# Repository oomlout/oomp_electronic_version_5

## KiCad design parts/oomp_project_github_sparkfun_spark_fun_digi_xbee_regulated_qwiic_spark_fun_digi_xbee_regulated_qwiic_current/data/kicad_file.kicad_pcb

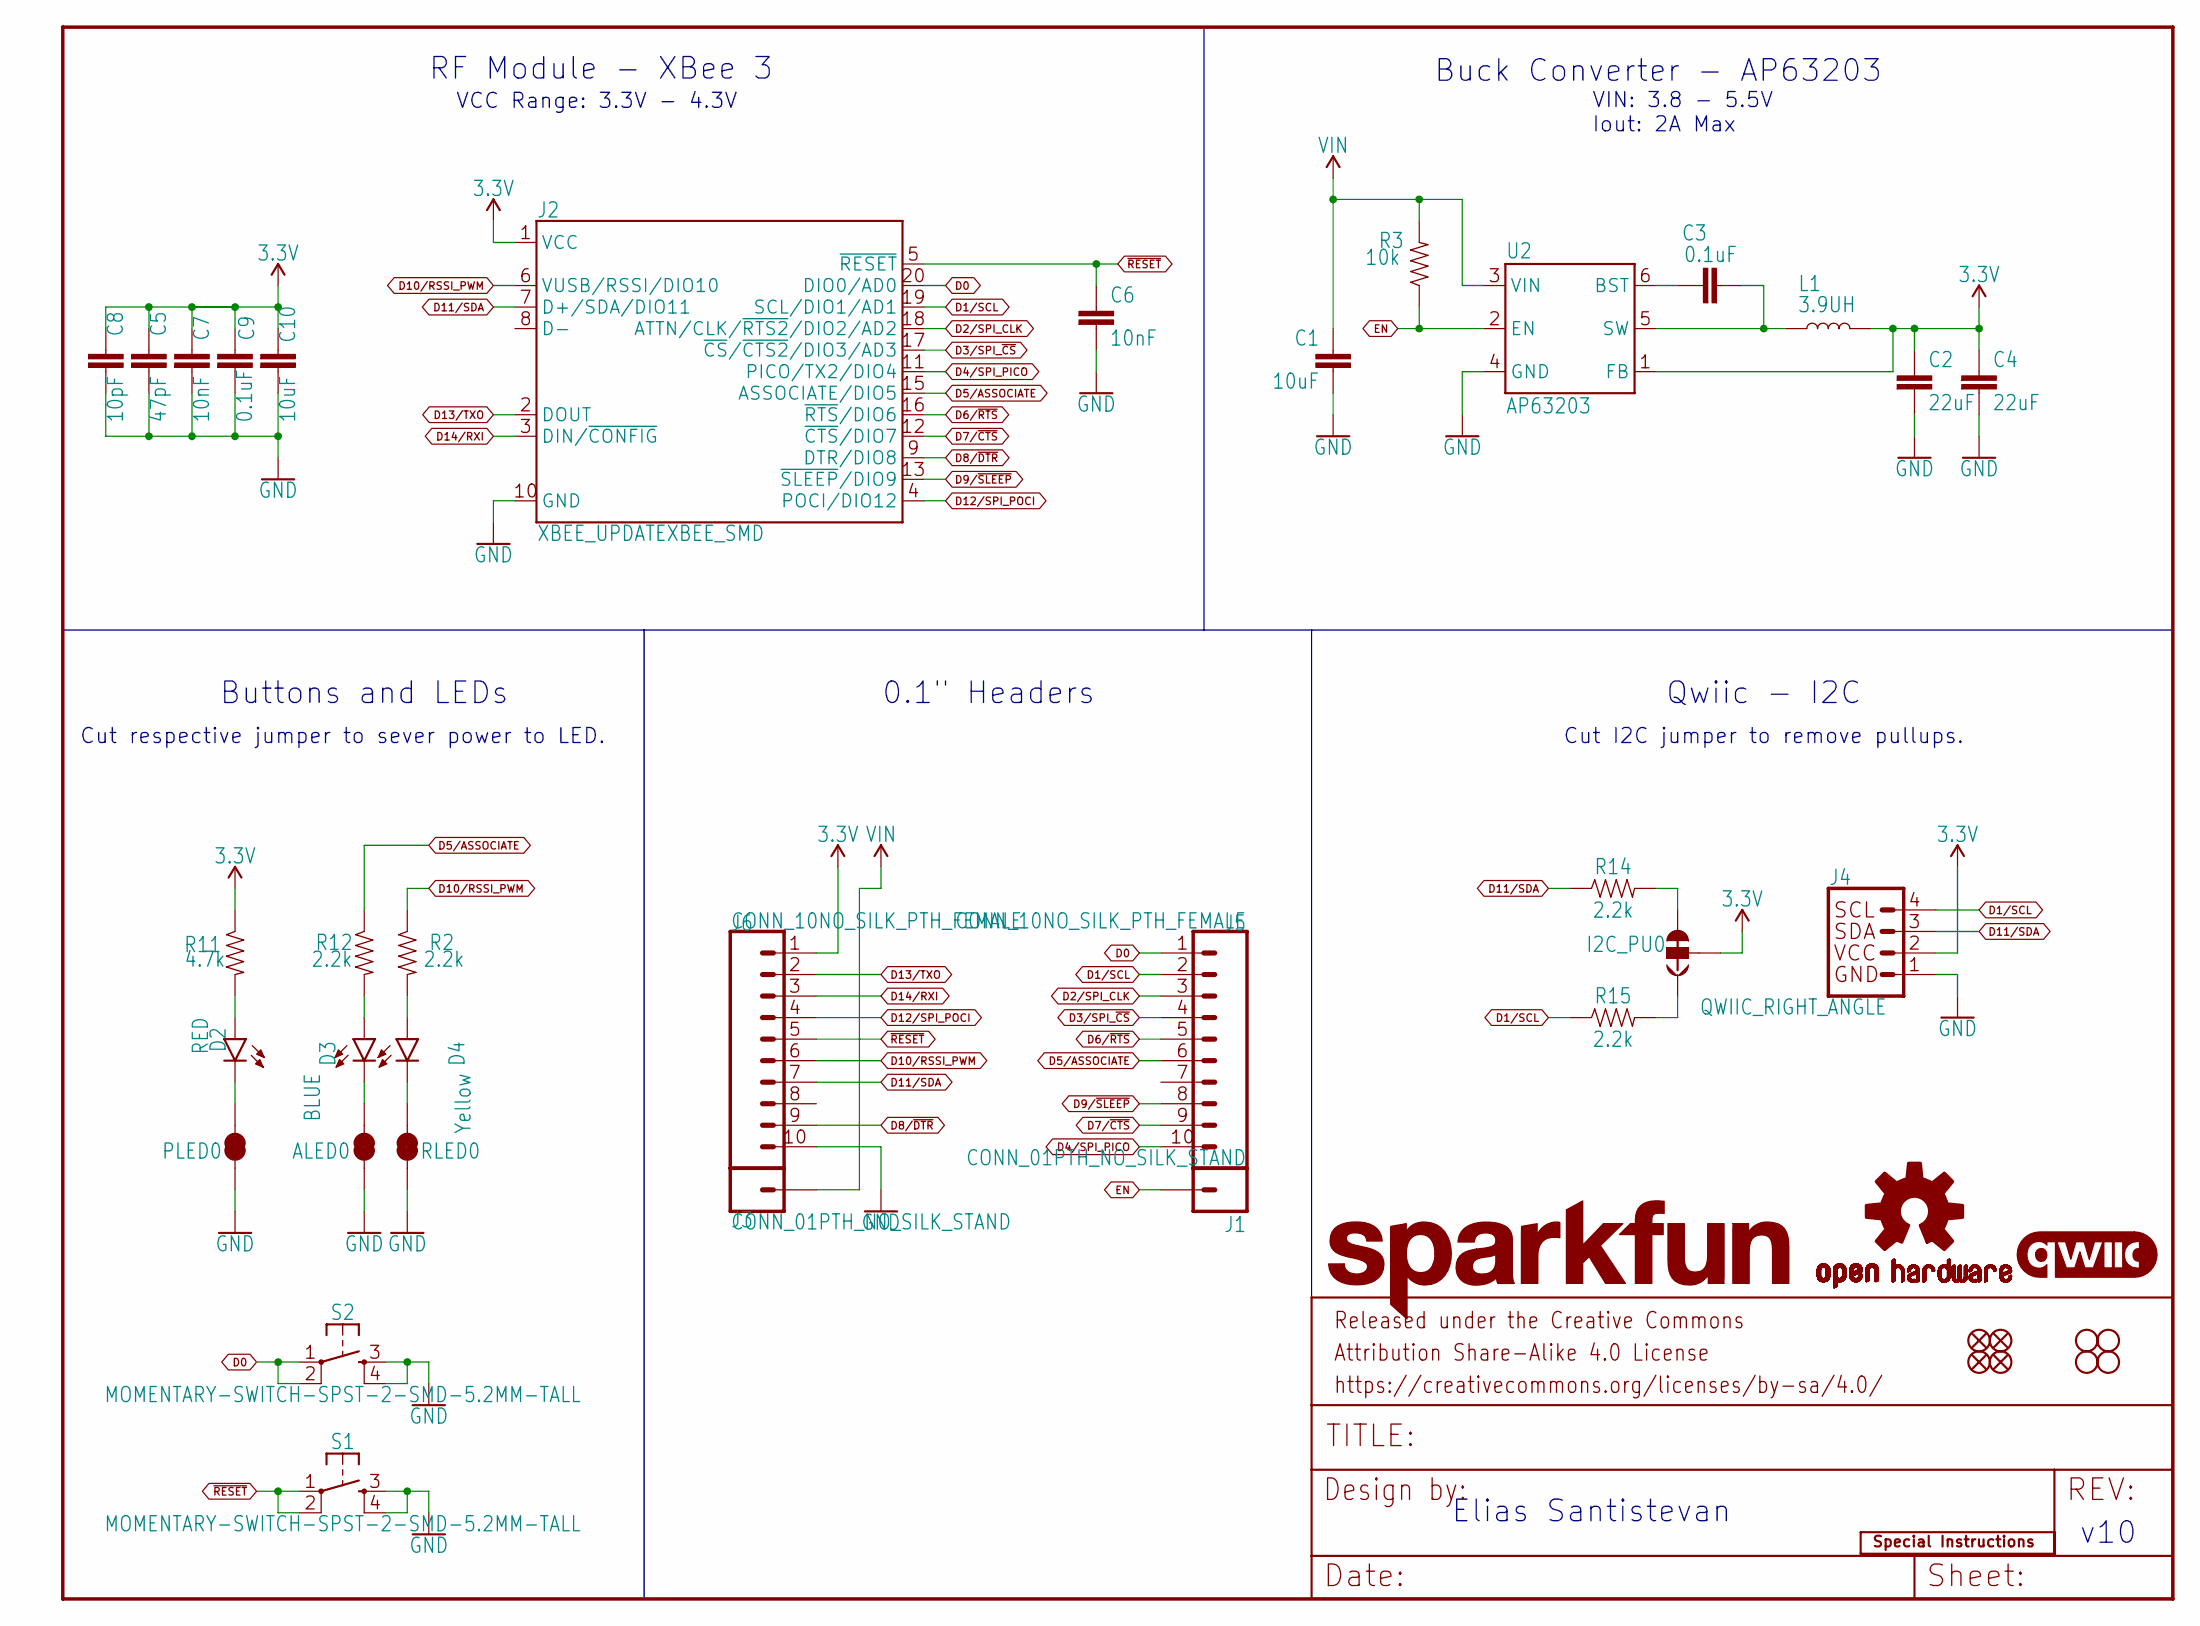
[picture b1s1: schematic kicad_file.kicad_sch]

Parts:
ALED0: JUMPER-SMT_2_NC_TRACE_SILK; SMT-JUMPER_2_NC_TRACE_SILK
C1: 10uF; 1210
C2, C4: 22uF; 0603
C3, C9: 0.1uF; 0603
C5: 47pF; 0603
C6, C7: 10nF; 0603
C8: 10pF; 0603
C10: 10uF; 0603
D2: RED; LED-0603
D3: BLUE; LED-0603
D4: Yellow; LED-0603
FD1, FD2, FD3, FD4: FIDUCIAL1X2; FIDUCIAL-1X2
FRAME2: FRAME-LETTER; CREATIVE_COMMONS
H1, H2, H3, H4: STAND-OFFTIGHT; STAND-OFF-TIGHT
I2C_PU0: JUMPER-SMT_3_2-NC_TRACE_SILK; SMT-JUMPER_3_2-NC_TRACE_SILK
J1, J3: CONN_01PTH_NO_SILK_STAND; 1X01_NO_SILK_STAND
J2: XBEE_UPDATEXBEE_SMD; XBEE3-SMD
J4: QWIIC_RIGHT_ANGLE; JST04_1MM_RA
J5, J6: CONN_10NO_SILK_PTH_FEMALE; 1X10_NO_SILK
L1: 3.9UH; INDUCTOR_3.9UH
LOGO1: SPECIAL_INSTRUCTIONS-ORDERING; ORDERING_INSTRUCTIONS
LOGO2: OSHW-LOGOS; OSHW-LOGO-S
LOGO3: QWIIC_LOGO_4MM; QWIIC_4MM
LOGO4: SFE_LOGO_NAMEBLANK; BLANK
PLED0: JUMPER-SMT_2_NC_TRACE_SILK; SMT-JUMPER_2_NC_TRACE_SILK
R2, R12, R14, R15: 2.2k; 0603
R3: 10k; 0603
R11: 4.7k; 0603
RLED0: JUMPER-SMT_2_NC_TRACE_SILK; SMT-JUMPER_2_NC_TRACE_SILK
S1, S2: MOMENTARY-SWITCH-SPST-2-SMD-5.2MM-TALL; TACTILE_SWITCH_SMD_5.2MM
U2: AP63203; SOT23-6

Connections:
3.3V: C2.1, C4.1, C5.1, C7.1, C8.1, C9.1, C10.1, I2C_PU0.2, J2.1 (VCC), J4.2, J6.1, L1.P$2 (2), R11.1, U2.1 (FB)
D0: J2.20 (DIO0/AD0), J5.1, S2.1, S2.2
D1/SCL: J2.19 (SCL/DIO1/AD1), J4.4, J5.2, R15.1
D2/SPI_CLK: J2.18 (ATTN/CLK/~RTS2/DIO2/AD2), J5.3
D3/SPI_~CS: J2.17 (~CS/~CTS2/DIO3/AD3), J5.4
D4/SPI_PICO: J2.11 (PICO/TX2/DIO4), J5.10
D5/ASSOCIATE: J2.15 (ASSOCIATE/DIO5), J5.6, R12.1
D6/~RTS: J2.16 (~RTS/DIO6), J5.5
D7/~CTS: J2.12 (~CTS/DIO7), J5.9
D8/~DTR: J2.9 (DTR/DIO8), J6.9
D9/~SLEEP: J2.13 (~SLEEP/DIO9), J5.8
D10/RSSI_PWM: J2.6 (VUSB/RSSI/DIO10), J6.6, R2.1
D11/SDA: J2.7 (D+/SDA/DIO11), J4.3, J6.7, R14.1
D12/SPI_POCI: J2.4 (POCI/DIO12), J6.4
D13/TXO: J2.2 (DOUT), J6.2
D14/RXI: J2.3 (DIN/~CONFIG), J6.3
EN: J1.1, R3.1, U2.2 (EN)
GND: ALED0.1, C1.2, C2.2, C4.2, C5.2, C6.2, C7.2, C8.2, C9.2, C10.2, J2.10 (GND), J4.1, J6.10, PLED0.1, RLED0.1, S1.3, S1.4, S2.3, S2.4, U2.4 (GND)
unnamed: C3.1, U2.6 (BST)
unnamed: D4.A, R2.2
unnamed: D4.C, RLED0.2
unnamed: D2.A, R11.2
unnamed: C3.2, L1.P$1 (1), U2.5 (SW)
unnamed: I2C_PU0.3, R14.2
unnamed: D3.A, R12.2
unnamed: I2C_PU0.1, R15.2
unnamed: ALED0.2, D3.C
unnamed: D2.C, PLED0.2
VIN: C1.1, J3.1, R3.2, U2.3 (VIN)
~RESET: C6.1, J2.5 (~RESET), J6.5, S1.1, S1.2

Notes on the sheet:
Buck Converter - AP63203
VCC Range: 3.3V - 4.3V
Elias Santistevan
0.1" Headers
RF Module - XBee 3
VIN: 3.8 - 5.5V Iout: 2A Max
Buttons and LEDs
v10
Qwiic - I2C
Cut I2C jumper to remove pullups.
Cut respective jumper to sever power to LED.

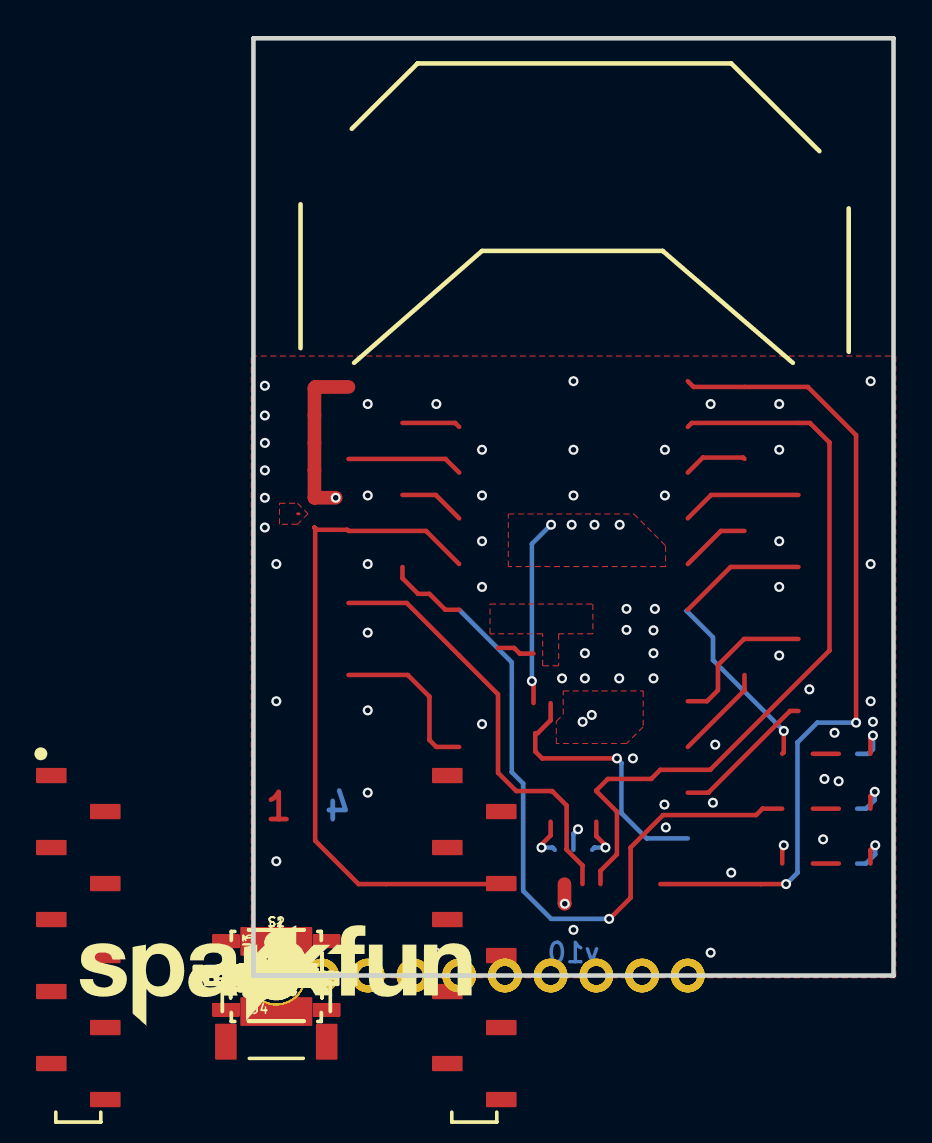
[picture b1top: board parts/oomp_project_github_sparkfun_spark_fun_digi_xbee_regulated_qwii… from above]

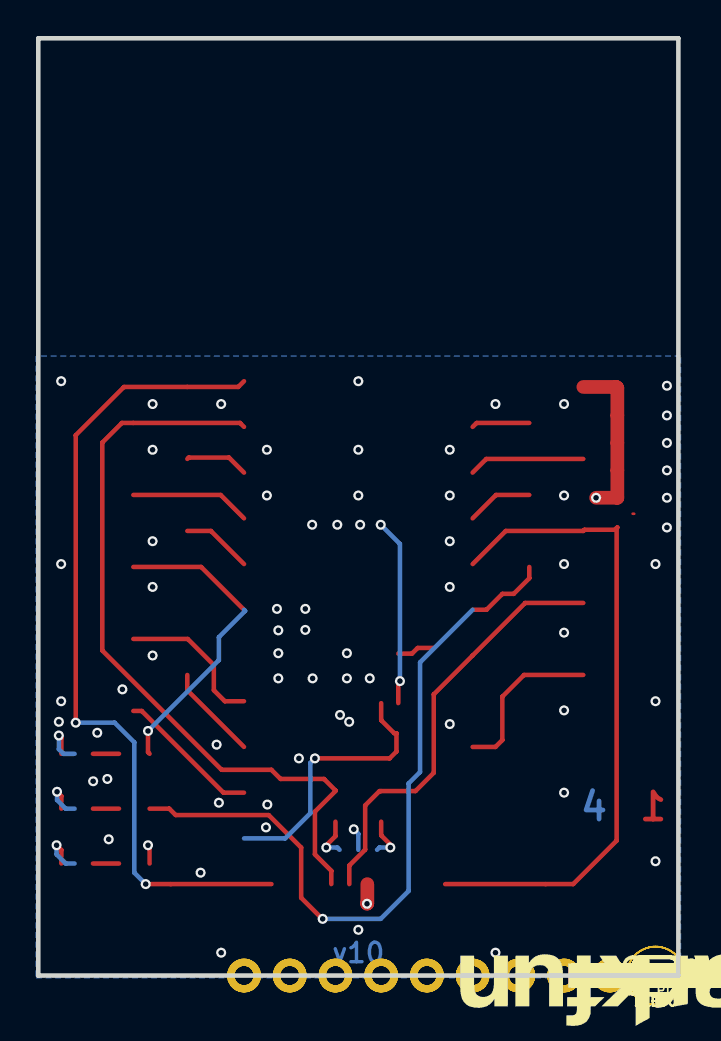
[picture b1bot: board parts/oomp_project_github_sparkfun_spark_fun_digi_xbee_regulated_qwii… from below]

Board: 4 copper layers, 35.6 x 52.1 mm, 98 parts (36 on the bottom side), 30 nets.

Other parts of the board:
U$1, U$12: #GND#0
U$2, U$63: SFE_LOGO_NAME_.2
U$3, U$6: #EN#17
U$4: #NC#1
U$5: #NC#3
U$7: #D7##CTS##26
U$8: #D0#AD0#18
U$9, U$44: #3V3#1
U$10: #D4#PICO#25
U$11: #RLED#22
U$13: #D8##DTR##27
U$14: #RSSI#D10#17
U$15: #SDA#D11#9
U$16: ##RST##15
U$17: #POCI#D12#24
U$18: #RXI#D14#15
U$19: #D2#AD2#19
U$20: #D6##RTS##25
U$21: #TXO#8
U$22: #TXO#D13#13
U$23, U$33: EXPLORER1344
U$24, U$29: REGULATED1343
U$25, U$28: XBEE340
U$26: #I2C#33
U$27: #RXI#7
U$30: #RST#30
U$31, U$65: #D0#3
U$32: #D1#AD1#SCL#8
U$34: #D3#AD3##CS##23
U$35: #D5#ASSOC#25
U$36: #D9##SLP##28
U$40: D03
U$42: PWR26
U$43: ASSOC27
U$45: #POCI#32
U$46, U$66: #VIN#4
U$49: #ALED#21
U$52: #PLED#20
U$59: ##CS##26
U$60: #SCLK#33
U$61: SFE_LOGO_FLAME_.2
U$62: RSSI31
U$64: #SCL#9

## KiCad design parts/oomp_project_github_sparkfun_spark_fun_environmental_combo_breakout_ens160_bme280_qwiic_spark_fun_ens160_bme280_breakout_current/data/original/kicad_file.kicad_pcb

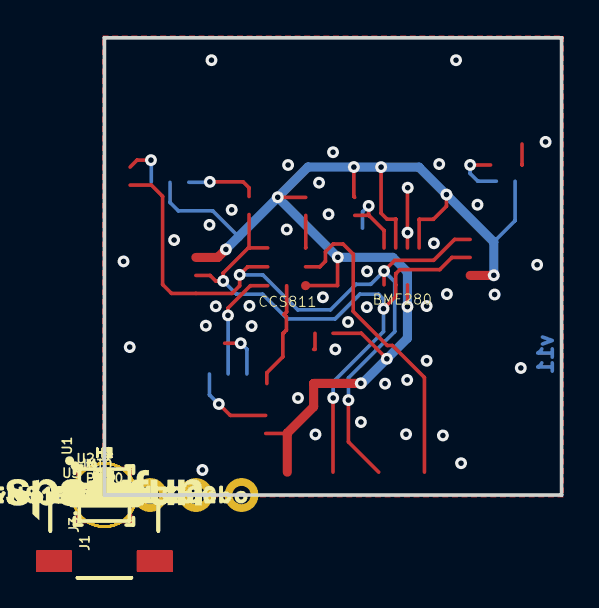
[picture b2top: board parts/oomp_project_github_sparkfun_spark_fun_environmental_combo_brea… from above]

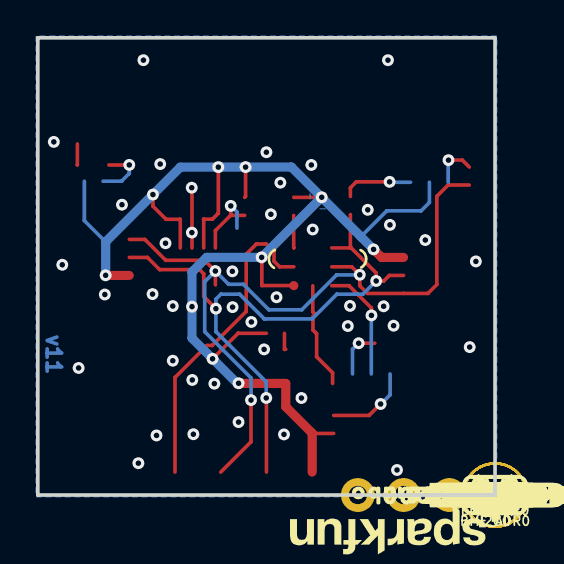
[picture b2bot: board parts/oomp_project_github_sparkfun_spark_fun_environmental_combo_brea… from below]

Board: 2 copper layers, 25.4 x 25.4 mm, 67 parts (25 on the bottom side), 16 nets.

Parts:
BME_ADR0: SMT-JUMPER_2_NO_SILK
C1, C3, C6: 0.1uF; 0402-TIGHT
C2, C5: 1.0uF; 0402-TIGHT
C4: 10uF; 0402-TIGHT
ENS_ADR0: JUMPER-SMT_3_1-NC_TRACE_SILK; SMT-JUMPER_3_1-NC_TRACE_SILK
FD1, FD2, FD3, FD4: FIDUCIAL1X2; FIDUCIAL-1X2
FRAME1: FRAME-LETTER; CREATIVE_COMMONS
H1, H2, H3, H4: STAND-OFF
I2C0: SMT-JUMPER_3_2-NC_TRACE_SILK
INT0: 1X01_NO_SILK_STAND
J1, J3: Qwiic Right Angle; JST04_1MM_RA
J4: PTH; 1X04_NO_SILK
LED0: SMT-JUMPER_2_NC_TRACE_SILK
LOGO1: SFE_LOGO_NAME.1_INCH; SFE_LOGO_NAME_.1
LOGO2: REVISION
LOGO3: SFE_LOGO_NAME.1_INCH; SFE_LOGO_NAME_.1@1
LOGO4: OSHW-LOGOS; OSHW-LOGO-S
PWR0: RED; LED-0603
R1, R6, R7, R8: 10k; 0402-TIGHT
R2: 4.7k; 0402-TIGHT
R3: 100k; 0402-TIGHT
R13, R14: 2.2k; 0402-TIGHT
U1: AP2127K-1.8V; SOT23-5
U2: ENS160; LGA-9
U3: BME280; LGA-8-2.5X2.5
U$1: #BME_ADR#0
U$2: #0X53#0
U$3: #0X52#0
U$4: ##INT##6
U$5: #ENS_ADR#0
U$6: #I2C#0
U$7, U$11: ENVIRONMENTAL_COMBO0
U$8: #SCL#4
U$9: #GND#2
U$10, U$12: ENS160_#_BME2800
U$13, U$61: DEFAULT0
U$14: #SDA#3
U$15: #PWR#0
U$16: OPEN#0X770
U$17: CLOSED#0X760
U$18: #LED#0
U$20, U$21: QWIIC_4MM
U$27, U$46: #3V3#874
U$45: #GND#864
U$47: #SDA#874
U$48: #SCL#875
U$51: ##INT##877
U$59: ORDERING_INSTRUCTIONS

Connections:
1.8V: C4.1, C5.1, U1.5, U2.P4
3.3V: C1.1, C2.1, C3.1, C6.1, I2C0.2, J1.2, J3.2, J4.2, LED0.1, R1.2, R3.2, R6.2, R8.2, U1.1, U2.P5, U3.2, U3.6, U3.8
ADDR: ENS_ADR0.2, U2.P3
GND: BME_ADR0.1, C1.2, C2.2, C3.2, C4.2, C5.2, C6.2, J1.1, J3.1, J4.1, R2.1, R7.1, U1.2, U2.P8, U2.P9, U3.1, U3.7
unnamed: ENS_ADR0.3, R8.1
unnamed: R1.1, U1.3
unnamed: I2C0.3, R13.2
unnamed: I2C0.1, R14.2
unnamed: PWR0.C, R2.2
unnamed: ENS_ADR0.1, R7.2
unnamed: LED0.2, PWR0.A
SCL: J1.4, J3.4, J4.4, R14.1, U2.P2, U3.4
SDA: J1.3, J3.3, J4.3, R13.1, U2.P1, U3.3
SDO/ADR: BME_ADR0.2, R3.1, U3.5
~CS: R6.1, U2.P7
~INT: INT0.1, U2.P6

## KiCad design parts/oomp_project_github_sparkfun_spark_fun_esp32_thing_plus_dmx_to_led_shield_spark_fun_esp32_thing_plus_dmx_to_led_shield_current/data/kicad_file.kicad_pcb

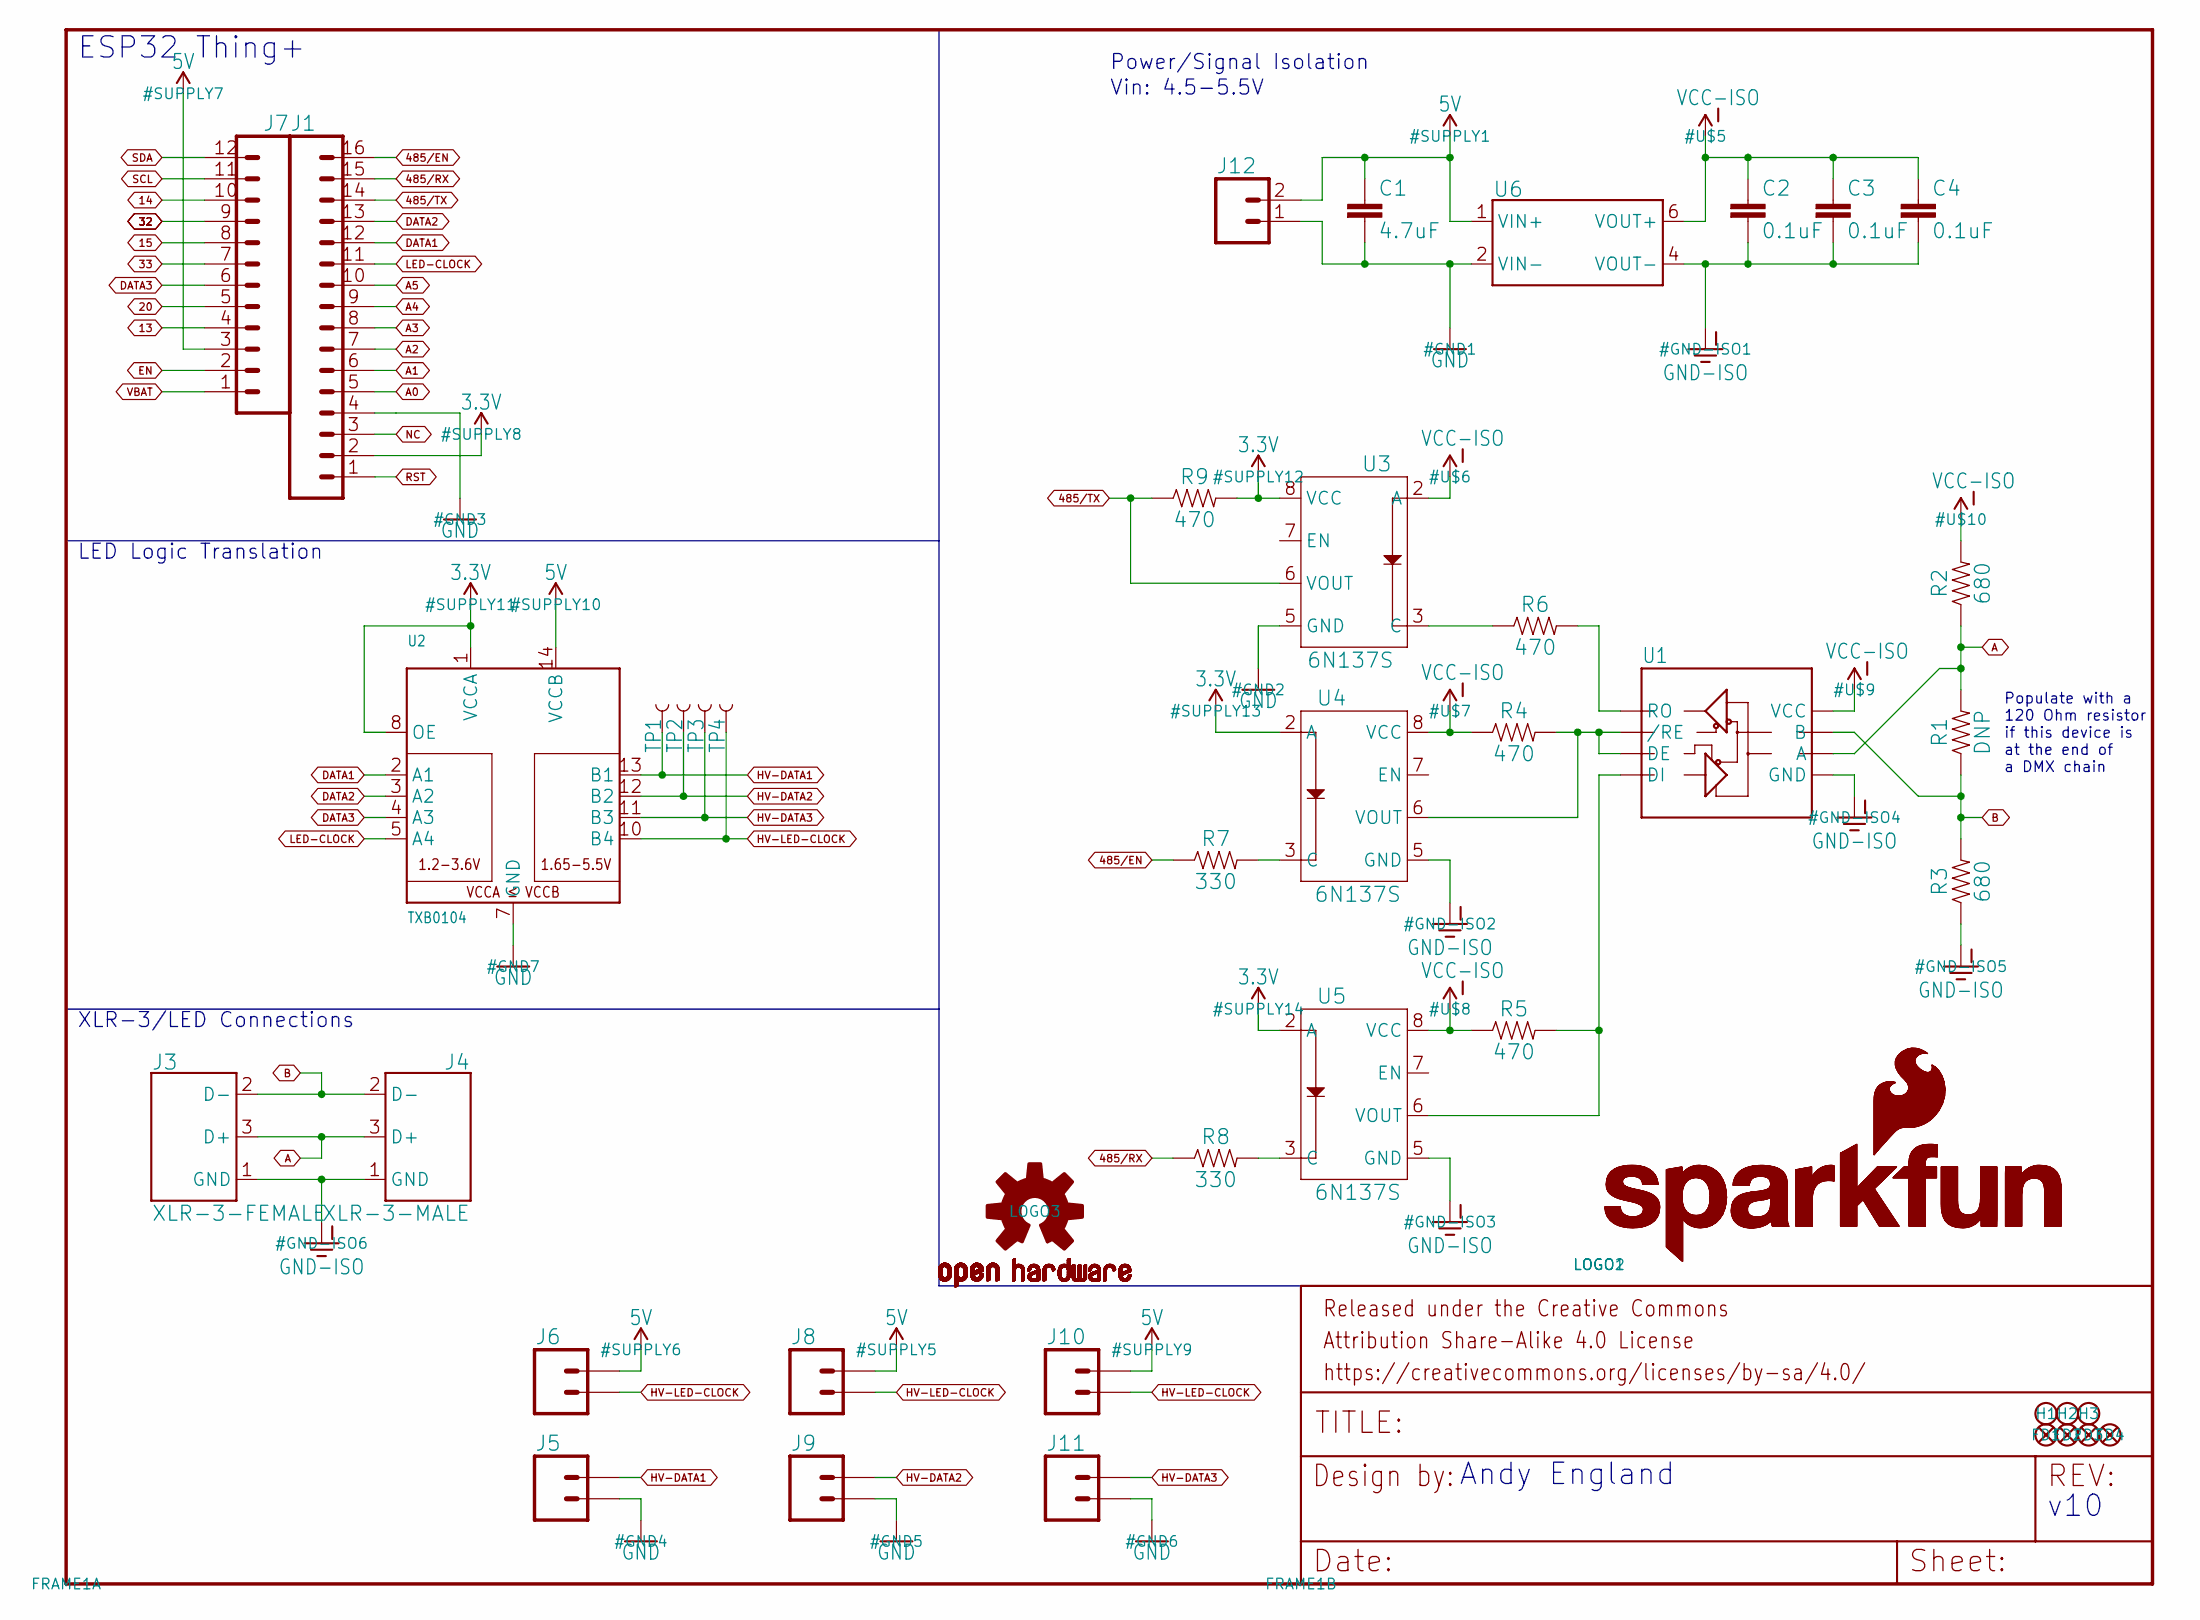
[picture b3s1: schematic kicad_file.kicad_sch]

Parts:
C1: 4.7uF; 0603
C2, C3, C4: 0.1uF; 0603
FD1, FD2, FD3, FD4: FIDUCIALUFIDUCIAL; FIDUCIAL-MICRO
FRAME1: FRAME-LETTER; CREATIVE_COMMONS
H1, H2, H3: STAND-OFFTIGHT; STAND-OFF-TIGHT
J1: CONN_16LOCK_NO_SILK; 1X16_LOCK_NO_SILK
J3: XLR-3-FEMALE; XLR-3_FEMALE
J4: XLR-3-MALE; XLR-3_MALE
J5, J6, J8, J9, J10, J11: CONN_02SMALL_POKEHOME; 1X02_POKEHOME
J7: CONN_12LOCK_NO_SILK; 1X12_LOCK_NO_SILK
J12: CONN_023.5MM; SCREWTERMINAL-3.5MM-2
LOGO1, LOGO2: SFE_LOGO_NAME_FLAME.2_INCH; SFE_LOGO_NAME_FLAME_.2
LOGO3: OSHW-LOGOS; OSHW-LOGO-S
R1: DNP; AXIAL-0.3EZ
R2, R3: 680; 0603
R4, R5, R6, R9: 470; 0603
R7, R8: 330; 0603
TP1, TP2, TP3, TP4: TEST-POINT3; PAD.03X.03
U1: MAX3485CSA; SO08
U2: TXB0104; TSSOP14
U3, U4, U5: 6N137S; 8-SMD
U6: RFB-0505S

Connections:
3.3V: J1.2, R9.2, U2.1 (VCCA), U2.8 (OE), U3.8 (VCC), U4.2 (A), U5.2 (A)
5V: C1.1, J6.P2 (2), J6.P4 (2), J7.3, J8.P2 (2), J8.P4 (2), J10.P2 (2), J10.P4 (2), J12.2, U2.14 (VCCB), U6.1 (VIN+)
13: J7.4
14: J7.10
15: J7.8
20: J7.5
32: J7.9
33: J7.7
485/EN: J1.16, R7.1
485/RX: J1.15, R8.1
485/TX: J1.14, R9.1, U3.6 (VOUT)
A: J3.3 (D+), J4.3 (D+), R1.P$2 (2), R2.1, U1.6 (A)
A0: J1.5
A1: J1.6
A2: J1.7
A3: J1.8
A4: J1.9
A5: J1.10
B: J3.2 (D-), J4.2 (D-), R1.P$1 (1), R3.2, U1.7 (B)
DATA1: J1.12, U2.2 (A1)
DATA2: J1.13, U2.3 (A2)
DATA3: J7.6, U2.4 (A3)
EN: J7.2
GND: C1.2, J1.4, J5.P1 (1), J5.P3 (1), J9.P1 (1), J9.P3 (1), J11.P1 (1), J11.P3 (1), J12.1, U2.7 (GND), U3.5 (GND), U6.2 (VIN-)
GND-ISO: C2.2, C3.2, C4.2, J3.1 (GND), J4.1 (GND), R3.1, U1.5 (GND), U4.5 (GND), U5.5 (GND), U6.4 (VOUT-)
HV-DATA1: J5.P2 (2), J5.P4 (2), TP1.P$1, U2.13 (B1)
HV-DATA2: J9.P2 (2), J9.P4 (2), TP2.P$1, U2.12 (B2)
HV-DATA3: J11.P2 (2), J11.P4 (2), TP3.P$1, U2.11 (B3)
HV-LED-CLOCK: J6.P1 (1), J6.P3 (1), J8.P1 (1), J8.P3 (1), J10.P1 (1), J10.P3 (1), TP4.P$1, U2.10 (B4)
LED-CLOCK: J1.11, U2.5 (A4)
unnamed: R8.2, U5.3 (C)
unnamed: R7.2, U4.3 (C)
unnamed: R4.2, U1.2 (/RE), U1.3 (DE), U4.6 (VOUT)
unnamed: R5.2, U1.4 (DI), U5.6 (VOUT)
unnamed: R6.1, U3.3 (C)
unnamed: R6.2, U1.1 (RO)
NC: J1.3
RST: J1.1
SCL: J7.11
SDA: J7.12
VBAT: J7.1
VCC-ISO: C2.1, C3.1, C4.1, R2.2, R4.1, R5.1, U1.8 (VCC), U3.2 (A), U4.8 (VCC), U5.8 (VCC), U6.6 (VOUT+)

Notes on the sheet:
v10
Andy England
Populate with a 120 Ohm resistor if this device is at the end of a DMX chain
Power/Signal Isolation
LED Logic Translation
ESP32 Thing+
Vin: 4.5-5.5V
XLR-3/LED Connections

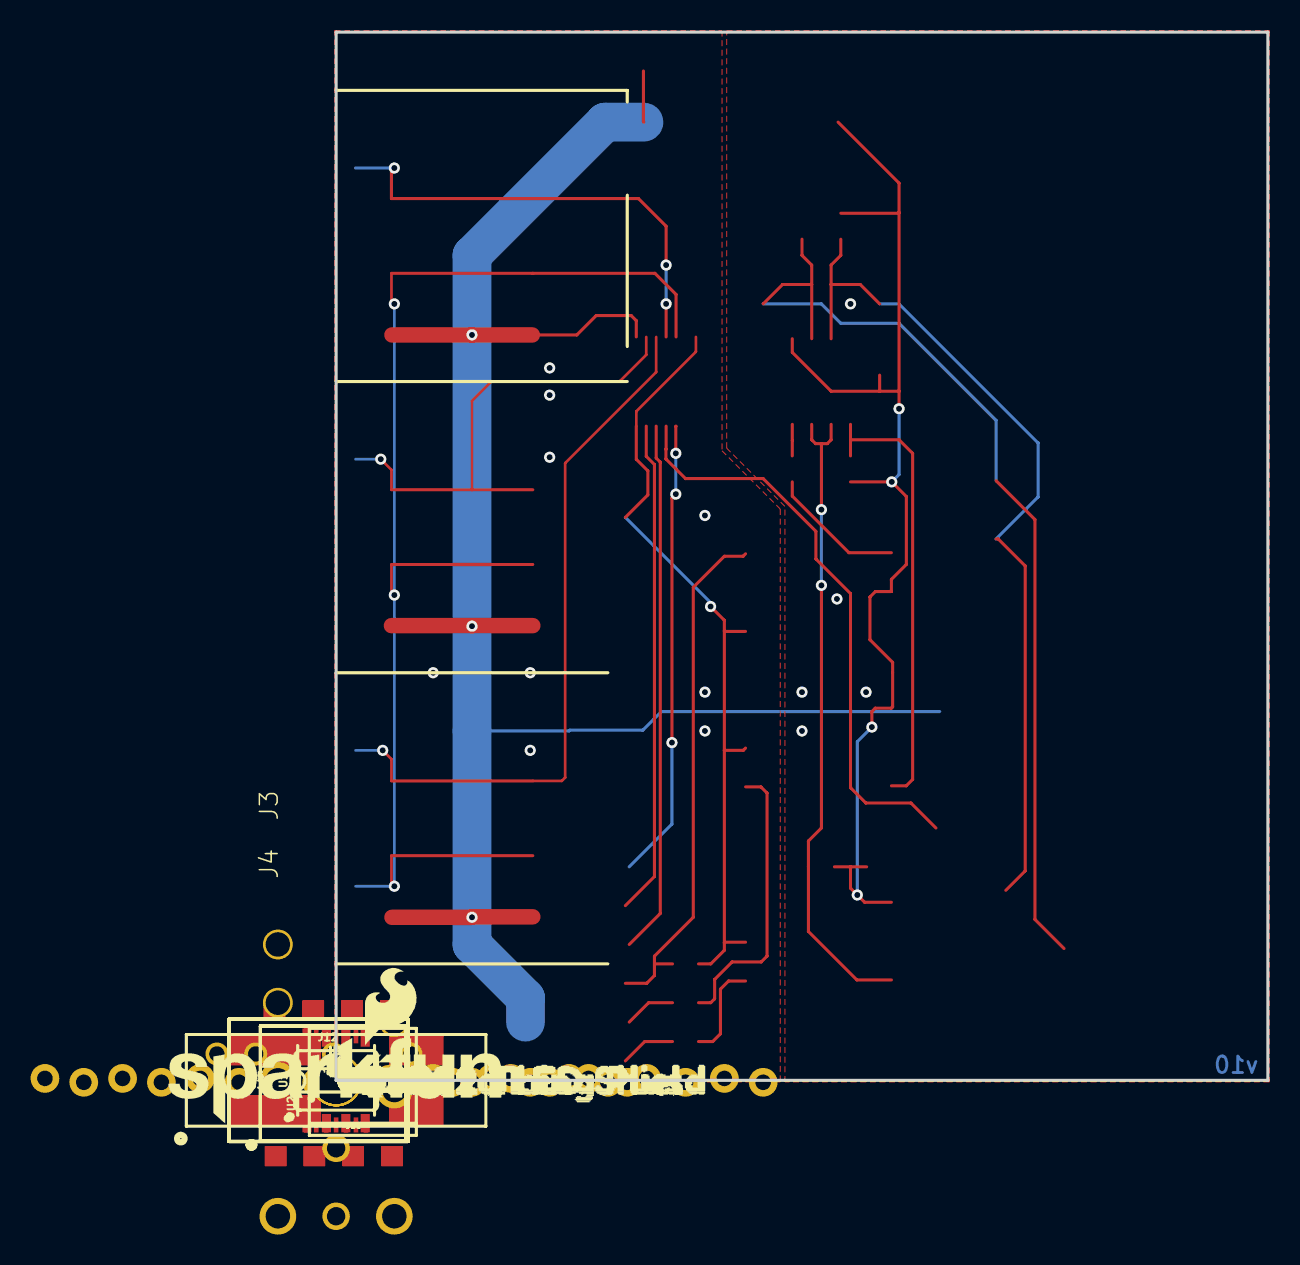
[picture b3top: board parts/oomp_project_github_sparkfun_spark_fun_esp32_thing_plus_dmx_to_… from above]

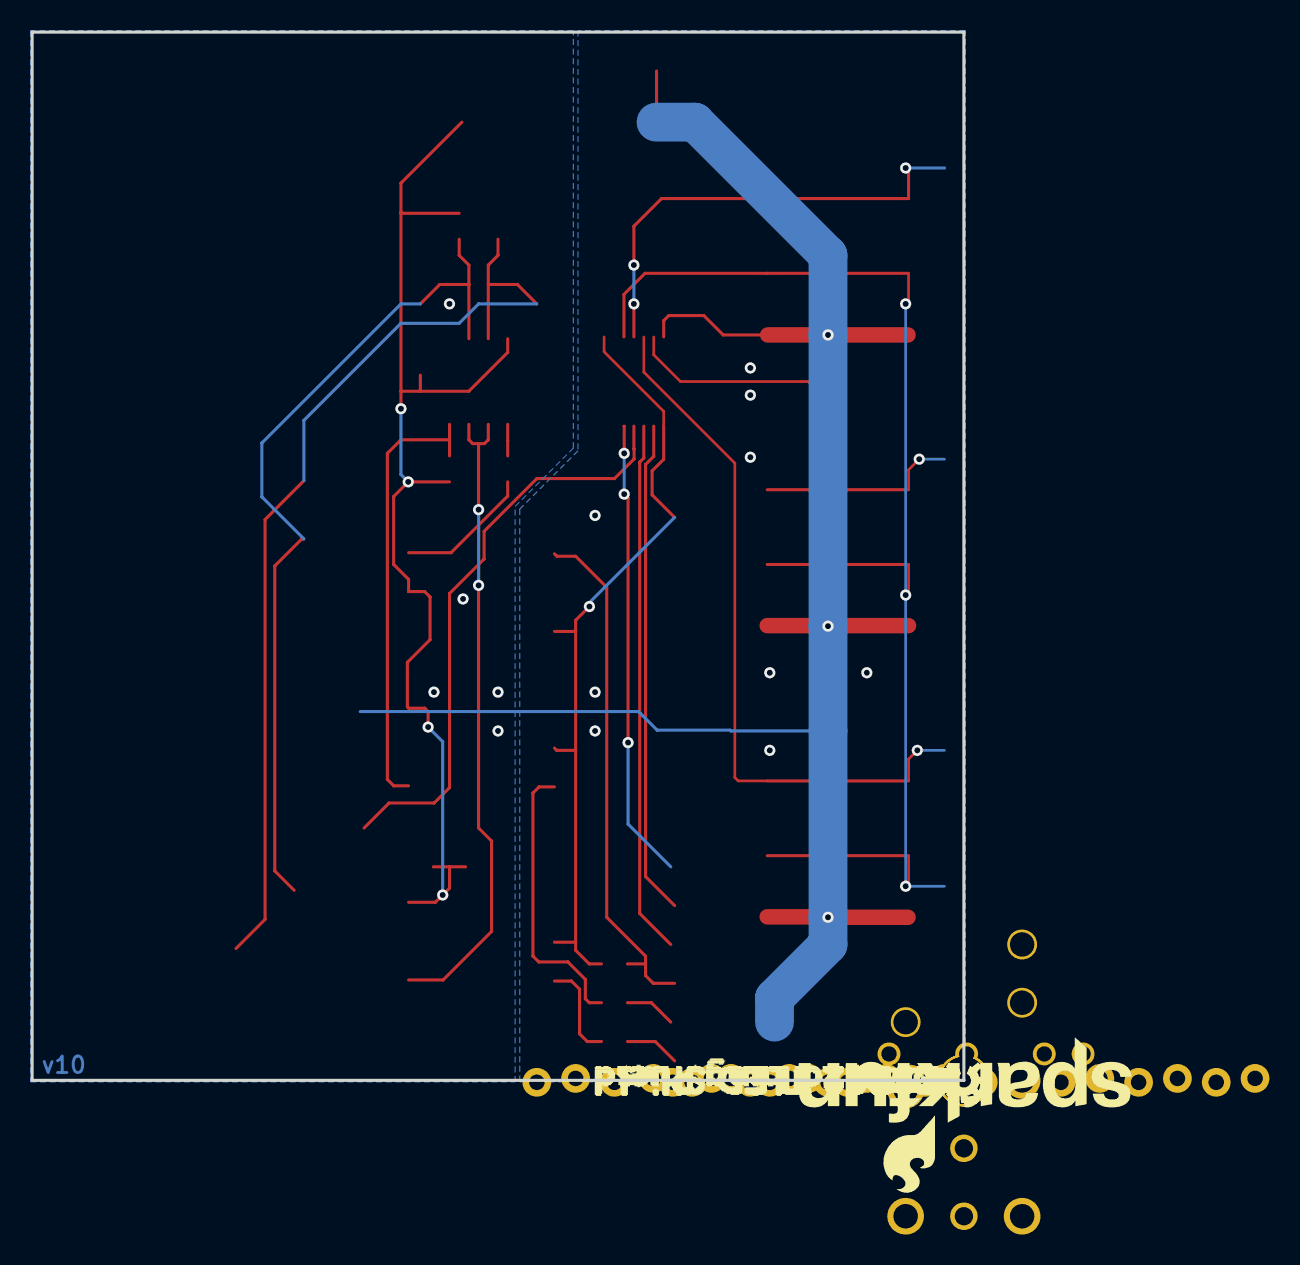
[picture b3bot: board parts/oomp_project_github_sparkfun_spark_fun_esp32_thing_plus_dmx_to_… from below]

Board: 2 copper layers, 61.0 x 68.6 mm, 65 parts (11 on the bottom side), 24 nets.

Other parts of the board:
U$1, U$2: __TERM__0
U$11, U$13: ESP32_THING_PLUS6
U$12, U$14: DMX_TO_LED_SHIELD7
U$15, U$17, U$21: 5V7
U$16: #0
U$18: C01
U$19: D00
U$20, U$24, U$28: G8
U$22: C12
U$23: D16
U$25: #1
U$26: C24
U$27: D23

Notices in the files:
parts/oomp_project_github_sparkfun_spark_fun_digi_xbee_regulated_qwiic_spark_fun_digi_xbee_regulated_qwiic_current/data/original/kicad_file.kicad_sch:
Released under the Creative Commons
https://creativecommons.org/licenses/by-sa/4.0
parts and their libraries:
Released under the Creative Commons Attribution Share-Alike 4.0 License
